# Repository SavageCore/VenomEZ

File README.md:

# VenomEZ
> GP2040-CE powered EZ Mod for Venom PS3/PS4 Arcade Stick

**TESTING** - do not order yet! v1.2 has just been delivered, Player LEDs are still not working, however, the rest of the board is fully functional (including Turbo LED!) and fitment is finally good. I'm working on a new version of the board, v1.3, which will fix the LED issues. Further down the line I'll rework to also add the USB connector found on the stock board so you can choose USB-C or not. Personally I am adding a Neutrik connector to my stick, so I don't need the stock connector.

"EZ" mod for the [Venom PS3/PS4 Arcade Stick](https://imgur.com/rmCg5gm), using the RP2040 microcontroller and [GP2040-CE](https://github.com/OpenStickCommunity/GP2040-CE) firmware. It's a drop-in replacement for the existing PCB, apart from the change to a USB-C connector.

## Firmware

Builds can be found [here](https://github.com/SavageCore/GP2040-CE/actions?query=is%3Asuccess+branch%3Afeature%2Fvenomez+event%3Apull_request) - these are pre-release builds and may not be stable and may lag behind the main branch.

## Pins

| GPIO | Function |
| --- | -------- |
17 | Up
16 | Down
14 | Left
15 | Right
5 | B1 / A / B / Cross / 2 / K1
6 | B2 / B / A / Circle / 3 / K2
13 | R2 / RT / ZR / R2 / 8 / K3
11 | L2 / LT / ZL / L2 / 7 / K4
7 | B3 / X / Y / Square / 1 / P1
8 | B4 / Y / X / Triangle / 4 / P2
12 | R1 / RB / R / R1 / 6 / P3
10 | L1 / LB / L / L1 / 5 / P4
19 | S1 / Back / Minus / Select / 9 / Coin
18 | S2 / Start / Plus / Start / 10 / Start
9 | A1 / Guide / Home / PS / 13 / ~
20 | A2 / ~ / Capture / ~ / 14 / ~
21 | Turbo
22 | LS/DP Toggle Switch (bound to LS slider add-on, LS position = D-Pad, DP = LS)
23 | Turbo 1/2 Toggle Switch (bound to RS slider add-on, Turbo 2 position = D-Pad, Turbo 1 = RS)
24 | PS3/PS4 Toggle Switch (bound to Focus Mode add-on, disables Start/Select/PS buttons)
25 | Player LED 1
26 | Player LED 2
27 | Player LED 3
28 | Player LED 4
29 | Turbo LED

## Ordering your own boards

1. Go to [JLCPCB](https://jlcpcb.com/)

2. Click on `Instant Quote`

3. Click on `Add Gerber file` and choose the file named `GERBER-VenomEZ.zip`
 from [Releases](https://github.com/SavageCore/VenomEZ/releases/latest)

4. Choose the following options for the board:

* Base Material = FR-4
* Layers = 2
* Dimensions = (should auto-populate) 71.97 mm x 41.99 mm
* PCB Qty = 5 (or more)
* Product Type = Industrial/Consumer electronics
* Different Design = 1
* Delivery Format = Single PCB
* PCB Thickness = 1.6
* PCB Color = Whatever you want
* Silkscreen = N/A
* Surface Finish = HASL(with lead)
* Outer Copper Weight = 1oz
* Via Covering = Tented
* Board Outline Tolerance = +/- 0.2mm (Regular)
* Confirm Production file = Yes
* **Remove Order Number = Specify a location**
* Flying Probe Test = Fully Test
* Gold Fingers = No
* Castellated Holes = No
* Edge Plating = No

Advanced options: (I left these as default)

* 4-Wire Kelvin Test = No
* Paper between PCBs = No
* Appearance Quality = IPC Class 2 Standard
* Silkscreen Technology = Ink-jet/Screen Printing Silkscreen
* Package Box = With JLCPCB logo

PCB Assembly:

* PCBA Type = Economic
* Assembly Side = Top Side
* PCBA Qty = (the same as PCB Qty)
* Tooling holes = Added by JLCPCB
* Confirm Parts Placement = Yes

## This is what we're replacing:

[![CC BY-SA 4.0][cc-by-sa-shield]][cc-by-sa]

[cc-by-sa]: http://creativecommons.org/licenses/by-sa/4.0/
[cc-by-sa-shield]: https://img.shields.io/badge/License-CC%20BY--SA%204.0-lightgrey.svg

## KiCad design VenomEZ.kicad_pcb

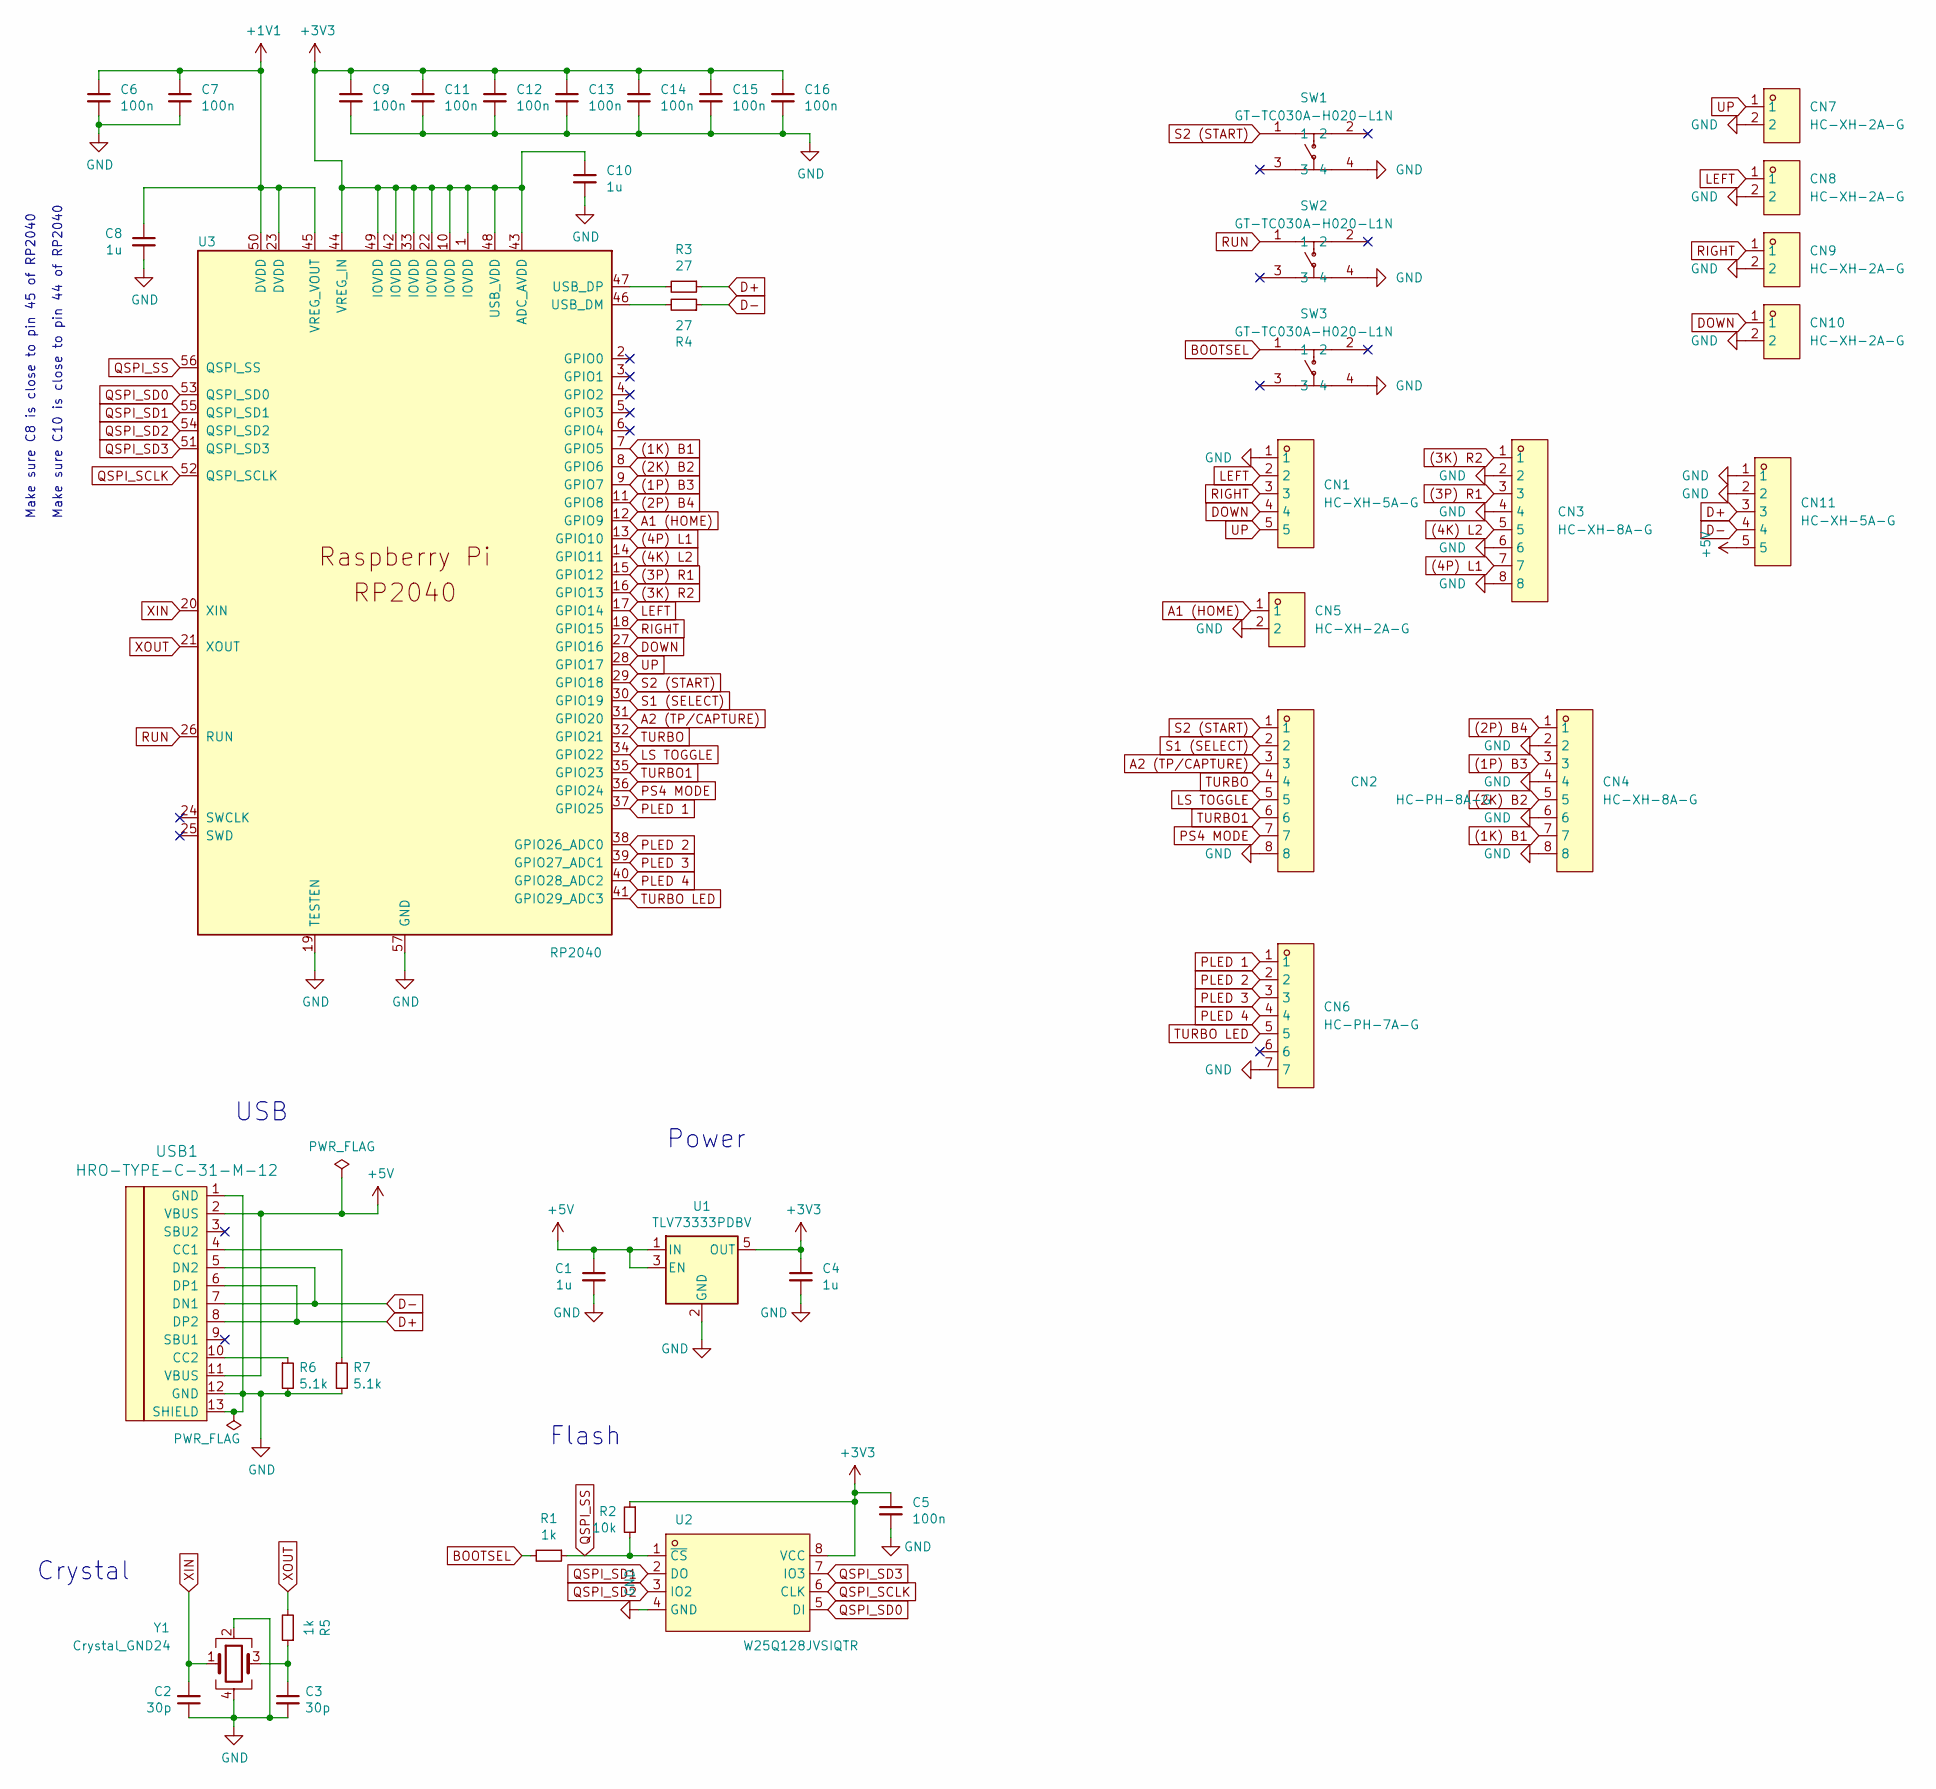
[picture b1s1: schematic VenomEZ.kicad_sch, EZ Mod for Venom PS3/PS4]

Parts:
C1, C4, C8, C10: 1u; C_0402_1005Metric; LCSC C52923
C2, C3: 30p; C_0402_1005Metric; LCSC C1570
C5, C6, C7, C9, C11, C12, C13, C14, C15, C16: 100n; C_0402_1005Metric; LCSC C1525
CN1, CN11: HC-XH-5A-G; CONN-TH_5P-P2.50_HC-XH-5A-G; LCSC Part C5341204
CN2: HC-PH-8A-G; CONN-TH_8P-P2.00_PH-8A; LCSC Part C33476
CN3, CN4: HC-XH-8A-G; CONN-TH_8P-P2.50_HCTL_XH-8A_C2908606; LCSC Part C5341207
CN5, CN7, CN8, CN9, CN10: HC-XH-2A-G; CONN-TH_2P-P2.50_HC-XH-2A-G; LCSC Part C5341201
CN6: HC-PH-7A-G; CONN-TH_7P-P2.00_PH-7A; LCSC Part C10398
R1, R5: 1k; R_0402_1005Metric; LCSC C11702
R2: 10k; R_0402_1005Metric; LCSC C25744
R3, R4: 27; R_0402_1005Metric; LCSC C138021
R6, R7: 5.1k; R_0402_1005Metric; LCSC C25905
SW1, SW2, SW3: GT-TC030A-H020-L1N; SW-SMD_4P-L3.6-W3.0-P1.50-LS4.7; LCSC Part C843670
U1: TLV73333PDBV; SOT-23-5; LCSC C134139
U2: W25Q128JVSIQTR; SOIC-8_L5.3-W5.3-P1.27-LS8.0-BL; LCSC Part C97521
U3: RP2040; RP2040-QFN-56; LCSC C2040
USB1: HRO-TYPE-C-31-M-12; HRO-TYPE-C-31-M-12-Assembly; LCSC C165948
Y1: Crystal_GND24; Crystal_SMD_3225-4Pin_3.2x2.5mm; LCSC C9002

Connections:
(1K) B1: CN4.7, U3.7 (GPIO5)
(1P) B3: CN4.3, U3.9 (GPIO7)
(2K) B2: CN4.5, U3.8 (GPIO6)
(2P) B4: CN4.1, U3.11 (GPIO8)
(3K) R2: CN3.1, U3.16 (GPIO13)
(3P) R1: CN3.3, U3.15 (GPIO12)
(4K) L2: CN3.5, U3.14 (GPIO11)
(4P) L1: CN3.7, U3.13 (GPIO10)
+1V1: C6.1, C7.1, C8.1, U3.23 (DVDD), U3.45 (VREG_VOUT), U3.50 (DVDD)
+3V3: C4.1, C5.1, C9.1, C10.1, C11.1, C12.1, C13.1, C14.1, C15.1, C16.1, R2.1, U1.5 (OUT), U2.8 (VCC), U3.1 (IOVDD), U3.10 (IOVDD), U3.22 (IOVDD), U3.33 (IOVDD), U3.42 (IOVDD), U3.43 (ADC_AVDD), U3.44 (VREG_IN), U3.48 (USB_VDD), U3.49 (IOVDD)
+5V: C1.1, CN11.5, U1.1 (IN), U1.3 (EN), USB1.2 (VBUS), USB1.11 (VBUS)
A1 (HOME): CN5.1, U3.12 (GPIO9)
A2 (TP/CAPTURE): CN2.3, U3.31 (GPIO20)
BOOTSEL: R1.2, SW3.1
D+: CN11.3, R3.1, USB1.6 (DP1), USB1.8 (DP2)
D-: CN11.4, R4.1, USB1.5 (DN2), USB1.7 (DN1)
DOWN: CN1.4, CN10.1, U3.27 (GPIO16)
GND: C1.2, C2.1, C3.2, C4.2, C5.2, C6.2, C7.2, C8.2, C9.2, C10.2, C11.2, C12.2, C13.2, C14.2, C15.2, C16.2, CN1.1, CN2.8, CN3.2, CN3.4, CN3.6, CN3.8, CN4.2, CN4.4, CN4.6, CN4.8, CN5.2, CN6.7, CN7.2, CN8.2, CN9.2, CN10.2, CN11.1, CN11.2, R6.2, R7.2, SW1.4, SW2.4, SW3.4, U1.2 (GND), U2.4 (GND), U3.19 (TESTEN), U3.57 (GND), USB1.1 (GND), USB1.12 (GND), USB1.13 (SHIELD), Y1.2, Y1.4
LEFT: CN1.2, CN8.1, U3.17 (GPIO14)
LS TOGGLE: CN2.5, U3.34 (GPIO22)
unnamed: C3.1, R5.1, Y1.3
unnamed: R4.2, U3.46 (USB_DM)
unnamed: R3.2, U3.47 (USB_DP)
unnamed: R7.1, USB1.4 (CC1)
unnamed: R6.1, USB1.10 (CC2)
PLED 1: CN6.1, U3.37 (GPIO25)
PLED 2: CN6.2, U3.38 (GPIO26_ADC0)
PLED 3: CN6.3, U3.39 (GPIO27_ADC1)
PLED 4: CN6.4, U3.40 (GPIO28_ADC2)
PS4 MODE: CN2.7, U3.36 (GPIO24)
QSPI_SCLK: U2.6 (CLK), U3.52 (QSPI_SCLK)
QSPI_SD0: U2.5 (DI), U3.53 (QSPI_SD0)
QSPI_SD1: U2.2 (DO), U3.55 (QSPI_SD1)
QSPI_SD2: U2.3 (IO2), U3.54 (QSPI_SD2)
QSPI_SD3: U2.7 (IO3), U3.51 (QSPI_SD3)
QSPI_SS: R1.1, R2.2, U2.1 (~CS), U3.56 (QSPI_SS)
RIGHT: CN1.3, CN9.1, U3.18 (GPIO15)
RUN: SW2.1, U3.26 (RUN)
S1 (SELECT): CN2.2, U3.30 (GPIO19)
S2 (START): CN2.1, SW1.1, U3.29 (GPIO18)
TURBO: CN2.4, U3.32 (GPIO21)
TURBO1: CN2.6, U3.35 (GPIO23)
TURBO LED: CN6.5, U3.41 (GPIO29_ADC3)
UP: CN1.5, CN7.1, U3.28 (GPIO17)
XIN: C2.2, U3.20 (XIN), Y1.1
XOUT: R5.2, U3.21 (XOUT)

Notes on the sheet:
Crystal
USB
Make sure C8 is close to pin 45 of RP2040
Power
Make sure C10 is close to pin 44 of RP2040
Flash

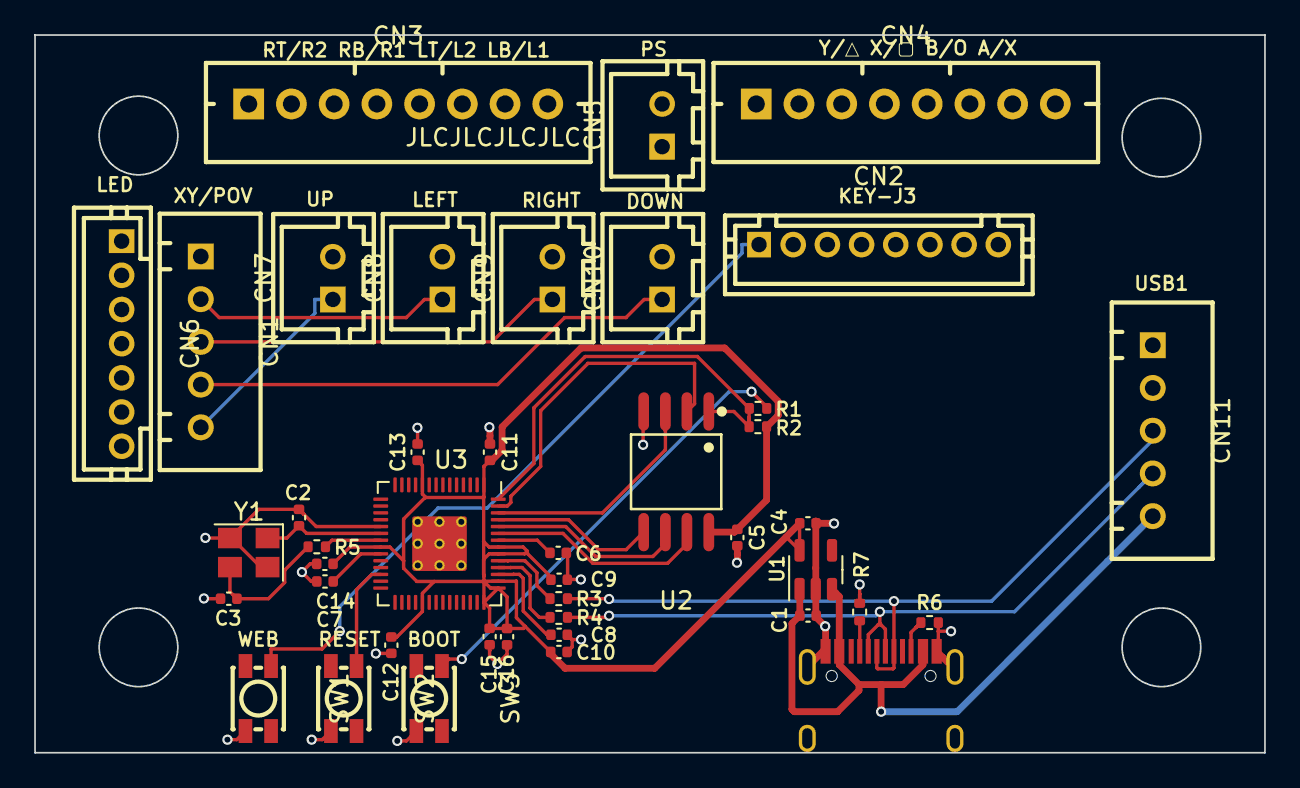
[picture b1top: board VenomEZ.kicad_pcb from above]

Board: 2 copper layers, 72.0 x 42.0 mm, 42 parts (0 on the bottom side), 46 nets.

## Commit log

2023-07-09 Add license
2023-07-10 Add logos
2023-07-10 WIP KiCad files
2023-07-10 Add version to silk, move github link to back of board
2023-07-10 Add ground fill
2023-07-11 Add WEB button
2023-07-11 Add RESET button
2023-07-11 LEDs need a resistor not capacitor?
2023-07-11 Change silk
2023-07-11 WIP embedded design
2023-07-11 Potentially finished RP2040
2023-07-12 Nearly all wired up?
2023-07-12 Add individual up, down, left and right connectors
2023-07-12 Update silk
2023-07-12 No DRC errors!
2023-07-12 Rename project files to VenomEZ
2023-07-12 Bring easyeda2kicad files into the project directory
2023-07-12 Silk updates
2023-07-13 Add hidden "JLCJLCJLCJLC"
2023-07-13 Update PH connectors to ones JLC stock
2023-07-13 Update new PH connectors 3d model file paths
2023-07-13 Add ordering instructions
2023-07-14 Remove unnecessary ground traces between direction headers
2023-07-14 Update some traces for better look
2023-07-14 Update to latest renders
    Renders as submitted to JLCPCB
2023-07-14 Add pins to readme
2023-07-31 Update top render
2023-07-31 Further silk improvements
2023-07-31 Most likely fixed LED. Mounting holes enlarged.
2023-07-31 Add gp2040-ce logo to rear of board
2023-07-31 Move web button up to the boot and reset buttons
2023-07-31 Update renders
2023-07-31 Remove CN2 from silk
2023-08-01 I think this is the correct mounting hole size!
2023-08-02 Correct LED pins
2023-08-07 Update testing notes in readme
2023-08-07 Bump revision of schematic
2023-08-07 Correct pins for v1.1 and firmware changes, add link to builds
2023-08-19 Enlarge mounting holes slightly
    They're a little tight fitting on v1.1
2024-02-14 Move buttons and R1/R2 for better clearance around screw
2024-03-10 Update readme with status
2024-03-11 Further readme improvements
2024-03-11 Move R1 and R2 closer together
    (cherry picked from commit ddfea70dafb84cfe39d8b151f37d746d716440b9)
2024-03-11 Update silk for 1.3
    (cherry picked from commit d50c346d8888544253aca363da94d46f0ae0f3f4)
2024-03-11 Very wip
2024-03-11 Started og usb connector / redesign
2024-03-11 Move R1 and R2 closer together
2024-03-11 Remove passthrough connector, not enough pins
2024-03-11 Move lcsc symbols to their own library
2024-03-11 Ignore #auto_saved_files#
